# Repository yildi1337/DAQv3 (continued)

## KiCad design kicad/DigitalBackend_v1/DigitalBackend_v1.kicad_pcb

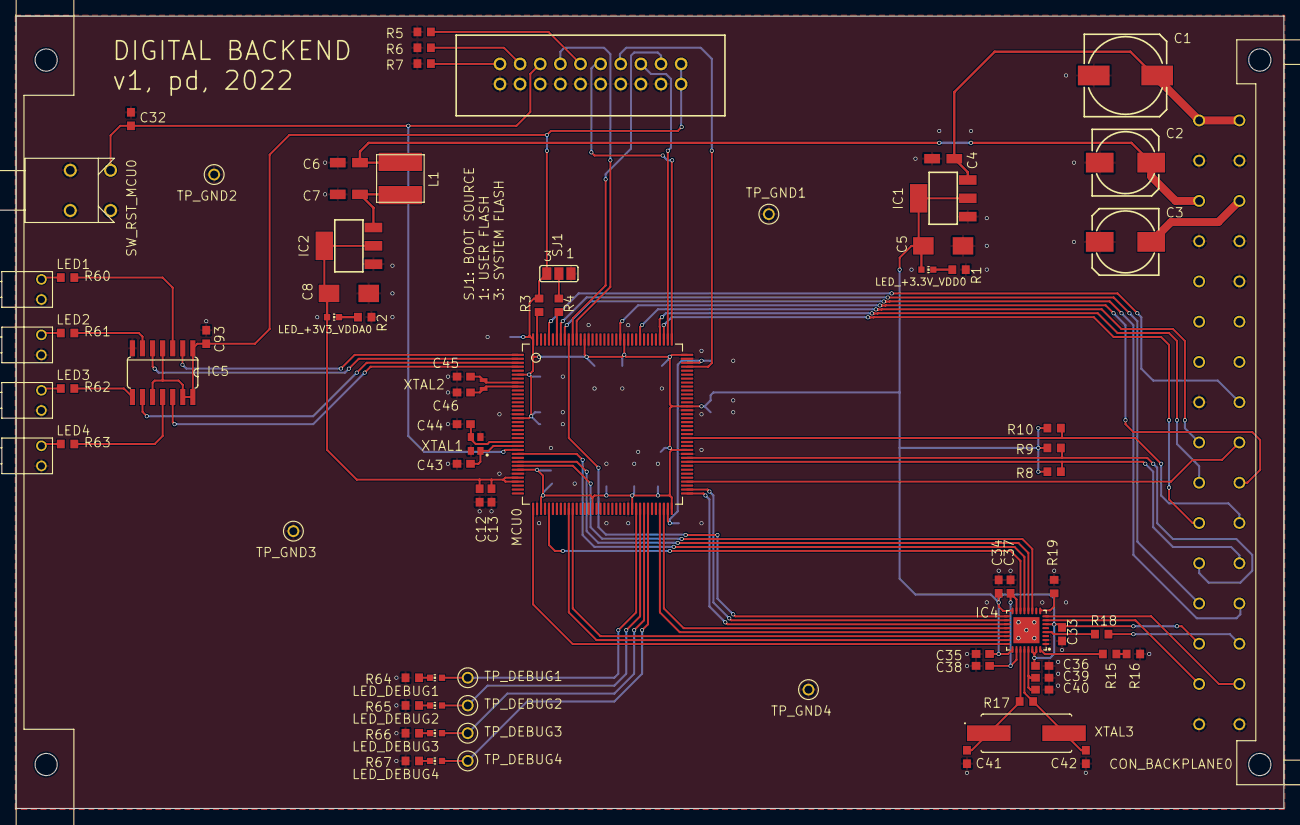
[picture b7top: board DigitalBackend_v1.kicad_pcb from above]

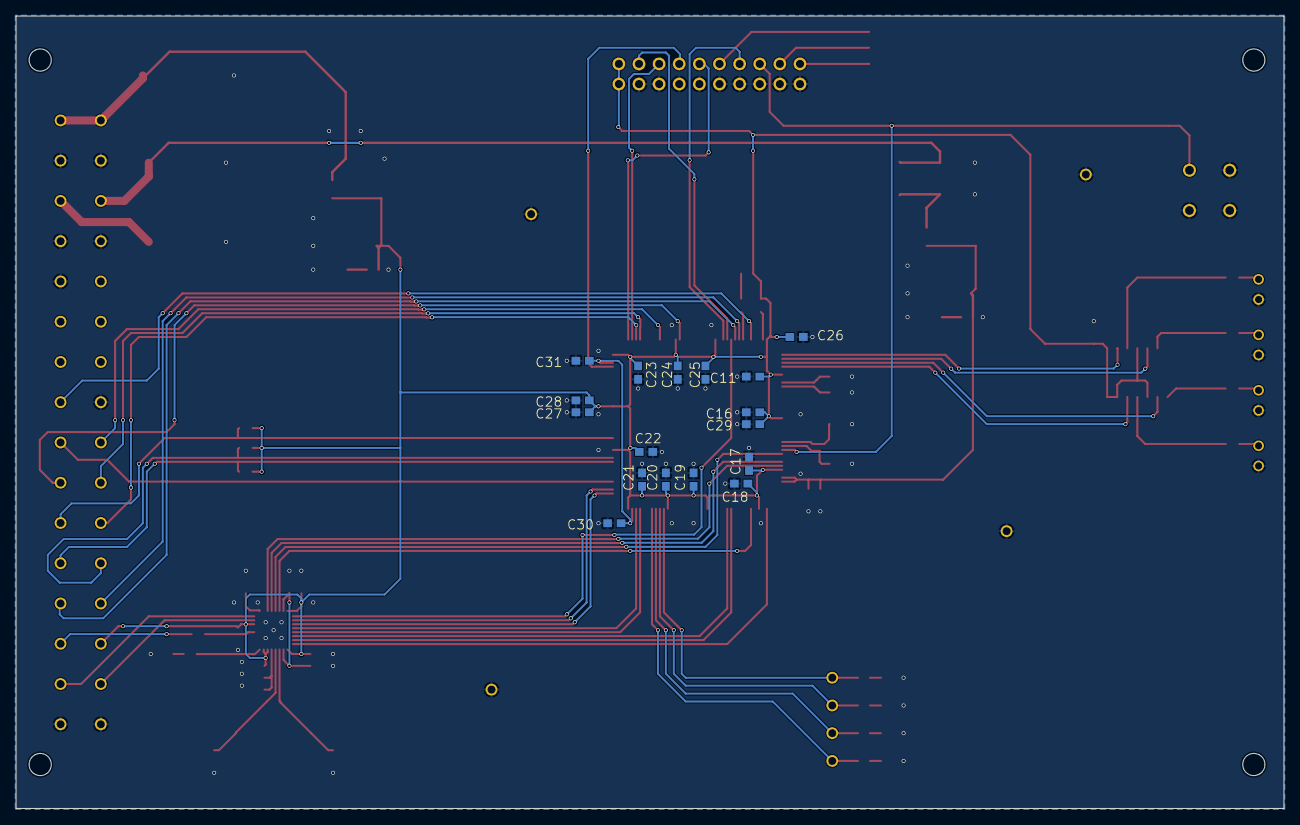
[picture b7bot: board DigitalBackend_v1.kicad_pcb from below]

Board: 2 copper layers, 160.0 x 100.0 mm, 98 parts (17 on the bottom side), 80 nets.

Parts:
C1: 1000u/16V; 153CLV-1010_18640681
C2, C3: 100u/25V; 153CLV-0810_18640681
C4, C6, C7: 10u; CT3216_23469469
C5, C8: 22u; CT6032_23469469
C11, C12, C27: 1u; C0603_23469469
C13, C16, C17, C18, C19, C20, C21, C22, C23, C24, C25, C26, C28, C32, C33, C34, C35, C36, C37, C40, C93: 100n; C0603_23469469
C29, C38, C39: 4.7u; C0603_23469469
C30, C31: 2.2u; C0603_23469469
C41, C42: 27p; C0603_23469469
C43, C44: 5.6p; C0603_23469469
C45, C46: 15p; C0603_23469469
CON_BACKPLANE0: 09031326921; 09031326921_33573412
CON_JTAG0: TST-110-01-T-DJ; TST-110-01-T-D_23500836
IC1: LM1117IMP-3.3; SOT223_23469477
IC2: LM1117IMP-3.3; SOT223_18698564
IC4: USB3300-EZK; USB3300-EZK_23525048
IC5: 74LVC126AD,112; SO14_85
L1: 100u; VLS6045AF-101M_31421361
LED1, LED2, LED3, LED4: 113-314-04; 113-314-04_33630242
LED_+3.3V_VDD0, LED_+3V3_VDDA0: CHIP-LED0603_259
LED_DEBUG1, LED_DEBUG2, LED_DEBUG3, LED_DEBUG4: CHIP-LED0603_259
MCU0: STM32H753ZIT6; LQFP144_23457850
PCB_BRACKET0: 60807-011; 60807-011_33573280
R1, R2, R64, R65, R66, R67: 750; R0603_23469469
R3, R4, R5, R6, R7, R16: 10k; R0603_23469469
R8, R9, R10: 1.5k; R0603_23469469
R15: 2k; R0603_23469469
R17: 1M; R0603_23469469
R18: 820; R0603_23469469
R19: 4.7k; R0603_23469469
R60, R61, R62, R63: 68; R0603_23469469
SJ1: SJ_2_23508320
SW_RST_MCU0: TP33W008000; TP33W008000_34733409
TP_DEBUG1, TP_DEBUG2, TP_DEBUG3, TP_DEBUG4: RSPRO-1MM-TERMINAL-POST-2622034; RSPRO-1MM-TERMINAL-POST-2622034_23908750
TP_GND1, TP_GND2, TP_GND3, TP_GND4: RSPRO-1MM-TERMINAL-POST-2622034_23908750
XTAL1: XRCGB25M000F2P00R0; XRCGB25M000F2P00R0_23510691
XTAL2: ABS05-32.768KHZ-T; ABS05-32.768KHZ-T_23609575
XTAL3: FOXSDLF-240F-20; FOXSDLF-240F-20_23537815

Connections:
+3V3_VDD: C5.+, C11.1, C16.1, C17.1, C18.1, C19.1, C20.1, C21.1, C22.1, C23.1, C24.1, C25.1, C26.1, C27.1, C28.1, C29.1, C33.1, C34.1, C35.1, C36.1, C93.2, CON_BACKPLANE0.27, CON_JTAG0.1, CON_JTAG0.2, IC1.2, IC1.TAB, IC4.6, IC4.16, IC4.25, IC4.30, IC4.31, IC5.1, IC5.4, IC5.10, IC5.13, IC5.14, LED_+3.3V_VDD0.A, MCU0.6, MCU0.17, MCU0.30, MCU0.39, MCU0.52, MCU0.62, MCU0.72, MCU0.84, MCU0.95, MCU0.108, MCU0.121, MCU0.131, MCU0.144, R3.2, R8.2, R9.2, R10.2, SJ1.3
+3V3_VDDA: C8.+, C12.1, C13.1, IC2.2, IC2.TAB, LED_+3V3_VDDA0.A, MCU0.32, MCU0.33
+5V: C1.+, C4.+, CON_BACKPLANE0.1, CON_BACKPLANE0.2, IC1.3
+12V: C2.+, C6.+, CON_BACKPLANE0.5, L1.1
-12V: C3.-, CON_BACKPLANE0.6
DEBUG1: LED_DEBUG1.A, MCU0.63, TP_DEBUG1.P$1
DEBUG2: LED_DEBUG2.A, MCU0.64, TP_DEBUG2.P$1
DEBUG3: LED_DEBUG3.A, MCU0.65, TP_DEBUG3.P$1
DEBUG4: LED_DEBUG4.A, MCU0.66, TP_DEBUG4.P$1
GND: C1.-, C2.-, C3.+, C4.-, C5.-, C6.-, C7.-, C8.-, C11.2, C12.2, C13.2, C16.2, C17.2, C18.2, C19.2, C20.2, C21.2, C22.2, C23.2, C24.2, C25.2, C26.2, C27.2, C28.2, C29.2, C30.2, C31.2, C32.1, C33.2, C34.2, C35.2, C36.2, C37.2, C38.2, C39.2, C40.2, C41.2, C42.2, C43.2, C44.2, C45.2, C46.2, C93.1, CON_BACKPLANE0.3, CON_BACKPLANE0.4, CON_BACKPLANE0.7, CON_BACKPLANE0.8, CON_BACKPLANE0.10, CON_BACKPLANE0.15, CON_BACKPLANE0.31, CON_BACKPLANE0.32, CON_JTAG0.4, CON_JTAG0.6, CON_JTAG0.8, CON_JTAG0.10, CON_JTAG0.12, CON_JTAG0.14, CON_JTAG0.16, CON_JTAG0.18, CON_JTAG0.20, IC1.1, IC2.1, IC4.1, IC4.2, IC4.33, IC5.7, LED1.-, LED2.-, LED3.-, LED4.-, MCU0.16, MCU0.31, MCU0.38, MCU0.51, MCU0.61, MCU0.83, MCU0.94, MCU0.107, MCU0.120, MCU0.130, R1.2, R2.2, R5.1, R6.1, R7.1, R16.1, R19.1, R64.2, R65.2, R66.2, R67.2, SJ1.1, SW_RST_MCU0.GND1, SW_RST_MCU0.GND2, SW_RST_MCU0.P1, TP_GND1.P$1, TP_GND2.P$1, TP_GND3.P$1, TP_GND4.P$1, XTAL1.2, XTAL1.4
I2C4_NINT: CON_BACKPLANE0.22, MCU0.87, R10.1
I2C4_SCL: CON_BACKPLANE0.24, MCU0.81, R8.1
I2C4_SDA: CON_BACKPLANE0.23, MCU0.82, R9.1
JTCK/SWCLK: CON_JTAG0.9, MCU0.109
JTDI: CON_JTAG0.5, MCU0.110
JTDO/TRACESWO: CON_JTAG0.13, MCU0.133
JTMS/SWDIO: CON_JTAG0.7, MCU0.105
LED1: IC5.2, MCU0.1
LED2: IC5.5, MCU0.2
LED3: IC5.9, MCU0.3
LED4: IC5.12, MCU0.4
unnamed: C37.1, C38.1, IC4.15, IC4.26
unnamed: MCU0.143, R3.1
unnamed: MCU0.138, R4.2
unnamed: C7.+, IC2.3, L1.2
unnamed: R4.1, SJ1.2
unnamed: CON_JTAG0.19, R7.2
unnamed: CON_JTAG0.17, R6.2
unnamed: CON_JTAG0.11, R5.2
unnamed: C45.1, MCU0.8, XTAL2.1
unnamed: C44.1, MCU0.23, XTAL1.3
unnamed: C43.1, MCU0.24, XTAL1.1
unnamed: C39.1, C40.1, IC4.29
unnamed: LED1.+, R60.2
unnamed: LED2.+, R61.2
unnamed: LED3.+, R62.2
unnamed: LED4.+, R63.2
unnamed: R15.1, R16.2
unnamed: IC4.32, R15.2
unnamed: C41.1, IC4.27, R17.2, XTAL3.1
unnamed: C42.1, IC4.28, R17.1, XTAL3.2
unnamed: IC4.4, R18.1
unnamed: IC4.9, R19.2
unnamed: C46.1, MCU0.9, XTAL2.2
unnamed: LED_+3.3V_VDD0.C, R1.1
unnamed: LED_+3V3_VDDA0.C, R2.1
unnamed: IC5.3, R60.1
unnamed: IC5.6, R61.1
unnamed: IC5.8, R62.1
unnamed: IC5.11, R63.1
unnamed: LED_DEBUG1.C, R64.1
unnamed: LED_DEBUG2.C, R65.1
unnamed: LED_DEBUG3.C, R66.1
unnamed: LED_DEBUG4.C, R67.1
NJTRST: CON_JTAG0.3, MCU0.134
NRST: C32.2, CON_JTAG0.15, MCU0.25, SW_RST_MCU0.P3
SPI2_MOSI: CON_BACKPLANE0.18, MCU0.76
SPI2_NSS: CON_BACKPLANE0.16, MCU0.140
SPI2_SCK: CON_BACKPLANE0.17, MCU0.117
SPI3_MISO: CON_BACKPLANE0.19, MCU0.112
SPI3_MOSI: CON_BACKPLANE0.20, MCU0.122
SPI3_SCK: CON_BACKPLANE0.21, MCU0.111
ULPI_CLK: IC4.14, MCU0.41
ULPI_DATA0: IC4.24, MCU0.37
ULPI_DATA1: IC4.23, MCU0.46
ULPI_DATA2: IC4.22, MCU0.47
ULPI_DATA3: IC4.21, MCU0.69
ULPI_DATA4: IC4.20, MCU0.70
ULPI_DATA5: IC4.19, MCU0.73
ULPI_DATA6: IC4.18, MCU0.74
ULPI_DATA7: IC4.17, MCU0.135
ULPI_DIR: IC4.12, MCU0.28
ULPI_NXT: IC4.11, MCU0.29
ULPI_STP: IC4.13, MCU0.26
USART1_RX: CON_BACKPLANE0.25, MCU0.137
USART1_TX: CON_BACKPLANE0.26, MCU0.136
USB_DATA_DM: CON_BACKPLANE0.30, IC4.8
USB_DATA_DP: CON_BACKPLANE0.29, IC4.7
VBUS_USB_DATA: CON_BACKPLANE0.28, R18.2
VCAP: C30.1, C31.1, MCU0.71, MCU0.106

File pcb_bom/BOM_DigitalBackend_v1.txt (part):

Qty Value                           Device                          Package                         Parts                                                                                                   Description                          POPULARITY SPICEPREFIX
6                                   LEDCHIP-LED0603                 CHIP-LED0603                    LED_+3.3V_VDD, LED_+3V3_VDDA, LED_DEBUG1, LED_DEBUG2, LED_DEBUG3, LED_DEBUG4                            LED                                  26                    
4                                   RSPRO-1MM-TERMINAL-POST-2622034 RSPRO-1MM-TERMINAL-POST-2622034 TP_GND1, TP_GND2, TP_GND3, TP_GND4                                                                                                                                 
1                                   SJ2W                            SJ_2                            SJ1                                                                                                     SMD solder JUMPER                    7                     
1   09031326921                     09031326921                     09031326921                     CON_BACKPLANE                                                                                                                                                      
3   1.5k                            R-EU_R0603                      R0603                           R8, R9, R10                                                                                             RESISTOR, European symbol            70         R          
1   1.8k                            R-EU_R0603                      R0603                           R2                                                                                                      RESISTOR, European symbol            70         R          
1   1000u/16V                       CPOL-EU153CLV-1010              153CLV-1010                     C1                                                                                                      POLARIZED CAPACITOR, European symbol 0          C          
21  100n                            C-EUC0603                       C0603                           C13, C16, C17, C18, C19, C20, C21, C22, C23, C24, C25, C26, C28, C32, C33, C34, C35, C36, C37, C40, C93 CAPACITOR, European symbol           73         C          
1   100u                            VLS6045AF-101M                  VLS6045AF-101M                  L1                                                                                                                                                                 
2   100u/25V                        CPOL-EU153CLV-0810              153CLV-0810                     C2, C3                                                                                                  POLARIZED CAPACITOR, European symbol 4          C          
6   10k                             R-EU_R0603                      R0603                           R3, R4, R5, R6, R7, R16                                                                                 RESISTOR, European symbol            70         R          
3   10u                             CPOL-EUCT3216                   CT3216                          C4, C6, C7                                                                                              POLARIZED CAPACITOR, European symbol 1          C          
4   113-314-04                      113-314-04                      113-314-04                      LED1, LED2, LED3, LED4                                                                                                                                             
2   15p                             C-EUC0603                       C0603                           C45, C46                                                                                                CAPACITOR, European symbol           73         C          
1   1M                              R-EU_R0603                      R0603                           R17                                                                                                     RESISTOR, European symbol            70         R          
3   1u                              C-EUC0603                       C0603                           C11, C12, C27                                                                                           CAPACITOR, European symbol           73         C          
2   2.2u                            C-EUC0603                       C0603                           C30, C31                                                                                                CAPACITOR, European symbol           73         C          
2   22u                             CPOL-EUCT6032                   CT6032                          C5, C8                                                                                                  POLARIZED CAPACITOR, European symbol 2          C          
2   27p                             C-EUC0603                       C0603                           C41, C42                                                                                                CAPACITOR, European symbol           73         C          
1   2k                              R-EU_R0603                      R0603                           R15                                                                                                     RESISTOR, European symbol            70         R          
1   4.7k                            R-EU_R0603                      R0603                           R19                                                                                                     RESISTOR, European symbol            70         R          
3   4.7u                            C-EUC0603                       C0603                           C29, C38, C39                                                                                           CAPACITOR, European symbol           73         C          
2   5.6p                            C-EUC0603                       C0603                           C43, C44                                                                                                CAPACITOR, European symbol           73         C          
1   60807-011                       60807-011                       60807-011                       PCB_BRACKET                                                                                                                                                        
4   68                              R-EU_R0603                      R0603                           R60, R61, R62, R63                                                                                      RESISTOR, European symbol            70         R          
1   74LVC126AD,112                  74AC126D                        SO14                            IC5                                                                                                     Quad bus BUFFER, 3-state             0                     
5   750                             R-EU_R0603                      R0603                           R1, R64, R65, R66, R67                                                                                  RESISTOR, European symbol            70         R          
1   820                             R-EU_R0603                      R0603                           R18                                                                                                     RESISTOR, European symbol            70         R          
1   ABS05-32.768KHZ-T               ABS05-32.768KHZ-T               ABS05-32.768KHZ-T               XTAL2                                                                                                                                                              
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
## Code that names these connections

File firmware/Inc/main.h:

/*
 *******************************************************************************
 * File:			main.h
 * Date:			2022-04-10
 * Author:			Phillip Durdaut
 * Summary:			Main include file with main program definitions
 * Notes:			-
 *******************************************************************************
 */

/* Define to prevent recursive inclusion -------------------------------------*/
#ifndef __MAIN_H
#define __MAIN_H

/* Includes ------------------------------------------------------------------*/
#include <stdio.h>
#include <stdlib.h>
#include <string.h>
#include <stdbool.h>
#include <stdint.h>
#include <float.h>
#include <ctype.h>

#include "stm32h7xx.h"
#include "stm32h7xx_hal.h"
#include "stm32h7xx_it.h"

#include "tca9534a.h"

/* Public defines ------------------------------------------------------------*/

/* ADC */
#define MAIN_ADC_SAMPLES_PER_SECOND						256e3
#define MAIN_ADC_SAMPLES_PER_MILLI_SECOND				256
#define MAIN_ADC_NUM_CHANNELS							4
#define MAIN_ADC_BYTES_PER_SAMPLE_PER_CHANNEL			4
#define MAIN_ADC_BYTES_PER_SAMPLE						(MAIN_ADC_NUM_CHANNELS * MAIN_ADC_BYTES_PER_SAMPLE_PER_CHANNEL)
#define MAIN_ADC_BYTES_PER_SECOND_PER_CHANNEL			(MAIN_ADC_BYTES_PER_SAMPLE_PER_CHANNEL * MAIN_ADC_SAMPLES_PER_SECOND)
#define MAIN_ADC_BYTES_PER_SECOND						(MAIN_ADC_NUM_CHANNELS * MAIN_ADC_BYTES_PER_SAMPLE_PER_CHANNEL * MAIN_ADC_SAMPLES_PER_SECOND)
#define MAIN_ADC_BYTES_PER_MILLI_SECOND_PER_CHANNEL		(MAIN_ADC_BYTES_PER_SAMPLE_PER_CHANNEL * MAIN_ADC_SAMPLES_PER_MILLI_SECOND)
#define MAIN_ADC_BYTES_PER_MILLI_SECOND					(MAIN_ADC_NUM_CHANNELS * MAIN_ADC_BYTES_PER_SAMPLE_PER_CHANNEL * MAIN_ADC_SAMPLES_PER_MILLI_SECOND)
#define MAIN_ADC_CLIPPING_VALUE							(4194304+100000)	/* slightly above 2.5 V */

/* USB */
#define MAIN_USB_VENDOR_ID								0x1337
#define MAIN_USB_PRODUCT_ID								0x0011
#define MAIN_USB_LANG_ID_STRING_US		 				0x0409
#define MAIN_USB_LANG_ID_STRING_DE		 				0x0407
#define MAIN_USB_LANG_ID_STRING							MAIN_USB_LANG_ID_STRING_US
#define MAIN_USB_MANUFACTURER_STRING	  				"pd"
#define MAIN_USB_PRODUCT_STRING							"DAQ v3"
#define MAIN_USB_SERIAL_STRING	 						"0000"
#define MAIN_USB_CONFIGURATION_STRING  					"DAQ v3 Config"
#define MAIN_USB_INTERFACE_STRING	  					"DAQ v3 Interface"
#define MAIN_USB_DEVICE_VERSION							0x0100

/* Interrupt priorities */
#define IRQ_UART1_PREEMPT_PRIORITY				2
#define IRQ_UART1_SUB_PRIORITY					2
#define IRQ_DMA1_STREAM0_PREEMPT_PRIORITY		10
#define IRQ_DMA1_STREAM0_SUB_PRIORITY			10
#define IRQ_OTG_HS_EP1_OUT_PREEMPT_PRIORITY		5
#define IRQ_OTG_HS_EP1_OUT_SUB_PRIORITY			5
#define IRQ_OTG_HS_EP1_IN_PREEMPT_PRIORITY		5
#define IRQ_OTG_HS_EP1_IN_SUB_PRIORITY			5
#define IRQ_OTG_HS_PREEMPT_PRIORITY				5
#define IRQ_OTG_HS_SUB_PRIORITY					5

/* Pins and ports */
#define LED_1_Pin 											GPIO_PIN_2
#define LED_1_Port 											GPIOE
#define LED_2_Pin 											GPIO_PIN_3
#define LED_2_Port 											GPIOE
#define LED_3_Pin 											GPIO_PIN_4
#define LED_3_Port 											GPIOE
#define LED_4_Pin 											GPIO_PIN_5
#define LED_4_Port 											GPIOE

#define DEBUG_1_Pin 										GPIO_PIN_10
#define DEBUG_1_Port 										GPIOE
#define DEBUG_2_Pin 										GPIO_PIN_11
#define DEBUG_2_Port 										GPIOE
#define DEBUG_3_Pin 										GPIO_PIN_12
#define DEBUG_3_Port 										GPIOE
#define DEBUG_4_Pin 										GPIO_PIN_13
#define DEBUG_4_Port 										GPIOE

#define UART1_TX_Pin										GPIO_PIN_6
#define UART1_TX_Port 										GPIOB
#define UART1_TX_AF 										GPIO_AF7_USART1
#define UART1_RX_Pin										GPIO_PIN_7
#define UART1_RX_Port 										GPIOB
#define UART1_RX_AF 										GPIO_AF7_USART1

#define SPI2_NSS_Pin 										GPIO_PIN_9
#define SPI2_NSS_Port 										GPIOB
#define SPI2_NSS_AF											GPIO_AF5_SPI2
#define SPI2_SCK_Pin 										GPIO_PIN_3
#define SPI2_SCK_Port 										GPIOD
#define SPI2_SCK_AF											GPIO_AF5_SPI2
#define SPI2_MOSI_Pin 										GPIO_PIN_15
#define SPI2_MOSI_Port 										GPIOB
#define SPI2_MOSI_AF										GPIO_AF5_SPI2

#define SPI3_SCK_Pin 										GPIO_PIN_10
#define SPI3_SCK_Port 										GPIOC
#define SPI3_SCK_AF											GPIO_AF6_SPI3
#define SPI3_MISO_Pin 										GPIO_PIN_11
#define SPI3_MISO_Port 										GPIOC
#define SPI3_MISO_AF										GPIO_AF6_SPI3
#define SPI3_MOSI_Pin 										GPIO_PIN_6
#define SPI3_MOSI_Port 										GPIOD
#define SPI3_MOSI_AF										GPIO_AF5_SPI3

#define USB_OTG_HS_ULPI_STP_Pin 							GPIO_PIN_0
#define USB_OTG_HS_ULPI_STP_Port 							GPIOC
#define USB_OTG_HS_ULPI_STP_AF								GPIO_AF10_OTG2_HS
#define USB_OTG_HS_ULPI_DIR_Pin 							GPIO_PIN_2
#define USB_OTG_HS_ULPI_DIR_Port 							GPIOC
#define USB_OTG_HS_ULPI_DIR_AF								GPIO_AF10_OTG2_HS
#define USB_OTG_HS_ULPI_NXT_Pin 							GPIO_PIN_3
#define USB_OTG_HS_ULPI_NXT_Port 							GPIOC
#define USB_OTG_HS_ULPI_NXT_AF								GPIO_AF10_OTG2_HS
#define USB_OTG_HS_ULPI_CK_Pin 								GPIO_PIN_5
#define USB_OTG_HS_ULPI_CK_Port 							GPIOA
#define USB_OTG_HS_ULPI_CK_AF								GPIO_AF10_OTG2_HS
#define USB_OTG_HS_ULPI_D0_Pin 								GPIO_PIN_3
#define USB_OTG_HS_ULPI_D0_Port 							GPIOA
#define USB_OTG_HS_ULPI_D0_AF								GPIO_AF10_OTG2_HS
#define USB_OTG_HS_ULPI_D1_Pin 								GPIO_PIN_0
#define USB_OTG_HS_ULPI_D1_Port 							GPIOB
#define USB_OTG_HS_ULPI_D1_AF								GPIO_AF10_OTG2_HS
#define USB_OTG_HS_ULPI_D2_Pin 								GPIO_PIN_1
#define USB_OTG_HS_ULPI_D2_Port 							GPIOB
#define USB_OTG_HS_ULPI_D2_AF								GPIO_AF10_OTG2_HS
#define USB_OTG_HS_ULPI_D3_Pin 								GPIO_PIN_10
#define USB_OTG_HS_ULPI_D3_Port 							GPIOB
#define USB_OTG_HS_ULPI_D3_AF								GPIO_AF10_OTG2_HS
#define USB_OTG_HS_ULPI_D4_Pin 								GPIO_PIN_11
#define USB_OTG_HS_ULPI_D4_Port 							GPIOB
#define USB_OTG_HS_ULPI_D4_AF								GPIO_AF10_OTG2_HS
#define USB_OTG_HS_ULPI_D5_Pin 								GPIO_PIN_12
#define USB_OTG_HS_ULPI_D5_Port 							GPIOB
#define USB_OTG_HS_ULPI_D5_AF								GPIO_AF10_OTG2_HS
#define USB_OTG_HS_ULPI_D6_Pin 								GPIO_PIN_13
#define USB_OTG_HS_ULPI_D6_Port 							GPIOB
#define USB_OTG_HS_ULPI_D6_AF								GPIO_AF10_OTG2_HS
#define USB_OTG_HS_ULPI_D7_Pin 								GPIO_PIN_5
#define USB_OTG_HS_ULPI_D7_Port 							GPIOB
#define USB_OTG_HS_ULPI_D7_AF								GPIO_AF10_OTG2_HS

#define I2C4_SCL_Port										GPIOD
#define I2C4_SCL_Pin										GPIO_PIN_12
#define I2C4_SCL_AF											GPIO_AF4_I2C4
#define I2C4_SDA_Port										GPIOD
#define I2C4_SDA_Pin										GPIO_PIN_13
#define I2C4_SDA_AF											GPIO_AF4_I2C4

/* I/O expander */
#define ADC_NRESET_DEVICE									TCA9534A_DEVICE_ACNV
#define ADC_NRESET_PIN										TCA9534A_PIN_0
#define ADC_SPI_NCS_DEVICE									TCA9534A_DEVICE_ACNV
#define ADC_SPI_NCS_PIN										TCA9534A_PIN_1
#define RD_NCS_DEVICE										TCA9534A_DEVICE_ACNV
#define RD_NCS_PIN											TCA9534A_PIN_2
#define RD_NRESET_DEVICE									TCA9534A_DEVICE_ACNV
#define RD_NRESET_PIN										TCA9534A_PIN_3

/* Public macros -------------------------------------------------------------*/
/* Public typedefs -----------------------------------------------------------*/
typedef uint8_t flag_t;
typedef enum
{
	CHANNEL_1 = 0,
	CHANNEL_2 = 1,
	CHANNEL_NONE
} channel_t;

/* Public variables ----------------------------------------------------------*/
extern flag_t MAIN_MeasurementRunning;
extern flag_t MAIN_SamplesRequested;

/* Public function prototypes ------------------------------------------------*/
extern void Error_Handler(void);

#endif /* __MAIN_H */

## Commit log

2022-07-30 Added pictures of modules
2022-07-30 Added step files of modules
2022-07-30 Added bom files
2022-07-30 Added gerber files
2022-07-30 Added pictures of the bare boards
2022-07-30 Added schematics
2022-07-30 Added EAGLE project files
2022-07-30 Updated bom files
2022-07-30 Updated gerber files
2022-07-30 Added complete CAD model
2022-07-31 Added missing pages
2022-08-11 Minor changes to 3D model
2022-09-24 Added firmware
2022-09-24 Added labview sources (data receiver)
2022-09-24 Added USB driver
2022-09-24 Added some noise measurements
2022-09-25 Added debug and control interface
2022-09-25 Added labview source code of signal analyzer
2022-09-25 Updated noise measurements
2022-09-25 Updated noise measurement results
2022-09-25 Added noise measurement results
2022-09-25 Updated measurement results
2022-09-26 Updated readme and noise plots
